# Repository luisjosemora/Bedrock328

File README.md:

# Bedrock328
Bedrock328 is an educational electronic board based on the ATmega328P microcontroller, designed to guide students and enthusiasts through every stage of embedded systems development — from through-hole soldering to bare-metal C programming and even Assembly coding.

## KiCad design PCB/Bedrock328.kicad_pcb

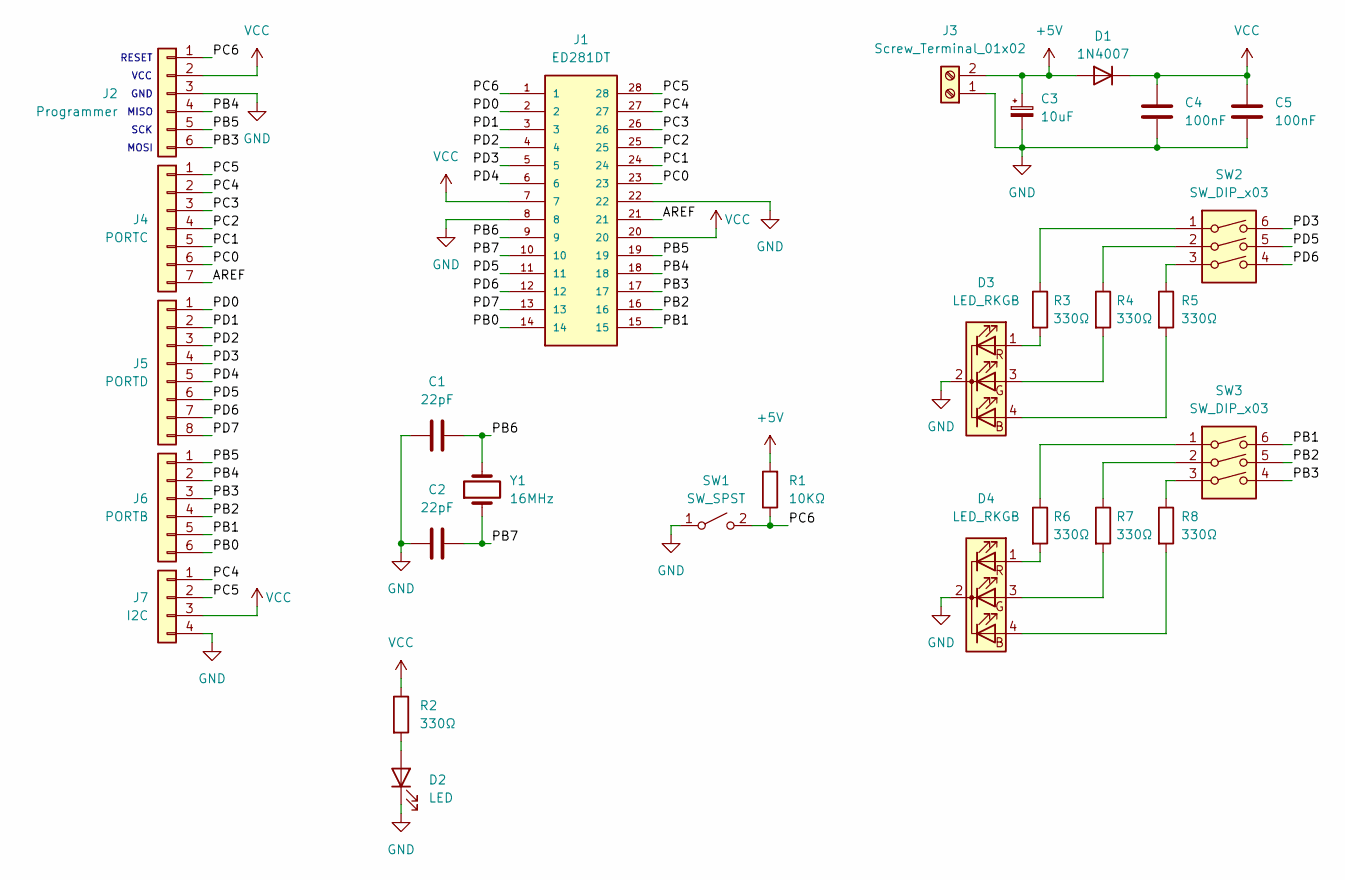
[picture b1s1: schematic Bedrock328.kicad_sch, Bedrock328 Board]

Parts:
C1, C2: 22pF; C_Disc_D5.0mm_W2.5mm_P5.00mm
C3: 10uF; CP_Radial_D8.0mm_P2.50mm
C4, C5: 100nF; C_Disc_D5.0mm_W2.5mm_P5.00mm
D1: 1N4007; D_DO-41_SOD81_P10.16mm_Horizontal
D2: LED; LED_D5.0mm
D3, D4: LED_RKGB; LED_D5.0mm-4_RGB
J1: ED281DT
J2: Programmer; PinHeader_1x06_P2.54mm_Vertical
J3: Screw_Terminal_01x02; KF301-2P
J4: PORTC; PinSocket_1x07_P2.54mm_Vertical
J5: PORTD; PinSocket_1x08_P2.54mm_Vertical
J6: PORTB; PinSocket_1x06_P2.54mm_Vertical
J7: I2C; PinSocket_1x04_P2.54mm_Vertical
R1: 10KΩ; R_Axial_DIN0207_L6.3mm_D2.5mm_P10.16mm_Horizontal
R2, R3, R4, R5, R6, R7, R8: 330Ω; R_Axial_DIN0207_L6.3mm_D2.5mm_P10.16mm_Horizontal
SW1: SW_SPST; SW_Tactile_6mm_round
SW2, SW3: SW_DIP_x03; SW_DIP_SPSTx03_Slide_9.78x9.8mm_W7.62mm_P2.54mm
Y1: 16MHz; Crystal_HC49-4H_Vertical

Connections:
+5V: C3.1, D1.2 (A), J3.2, R1.2
/AREF: J1.21, J4.7
/PB0: J1.14, J6.6
/PB1: J1.15, J6.5, SW3.6
/PB2: J1.16, J6.4, SW3.5
/PB3: J1.17, J2.6, J6.3, SW3.4
/PB4: J1.18, J2.4, J6.2
/PB5: J1.19, J2.5, J6.1
/PB6: C1.1, J1.9, Y1.2
/PB7: C2.1, J1.10, Y1.1
/PC0: J1.23, J4.6
/PC1: J1.24, J4.5
/PC2: J1.25, J4.4
/PC3: J1.26, J4.3
/PC4: J1.27, J4.2, J7.1
/PC5: J1.28, J4.1, J7.2
/PC6: J1.1, J2.1, R1.1, SW1.2 (B)
/PD0: J1.2, J5.1
/PD1: J1.3, J5.2
/PD2: J1.4, J5.3
/PD3: J1.5, J5.4, SW2.6
/PD4: J1.6, J5.5
/PD5: J1.11, J5.6, SW2.5
/PD6: J1.12, J5.7, SW2.4
/PD7: J1.13, J5.8
GND: C1.2, C2.2, C3.2, C4.2, C5.2, D2.1 (K), D3.2 (K), D4.2 (K), J1.8, J1.22, J2.3, J3.1, J7.4, SW1.1 (A)
unnamed: D2.2 (A), R2.2
unnamed: D3.4 (BA), R5.2
unnamed: D3.3 (GA), R4.2
unnamed: D3.1 (RA), R3.2
unnamed: D4.4 (BA), R8.2
unnamed: D4.3 (GA), R7.2
unnamed: D4.1 (RA), R6.2
unnamed: R3.1, SW2.1
unnamed: R4.1, SW2.2
unnamed: R5.1, SW2.3
unnamed: R6.1, SW3.1
unnamed: R7.1, SW3.2
unnamed: R8.1, SW3.3
VCC: C4.1, C5.1, D1.1 (K), J1.7, J1.20, J2.2, J7.3, R2.1

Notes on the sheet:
MOSI
VCC
SCK
RESET
GND
MISO

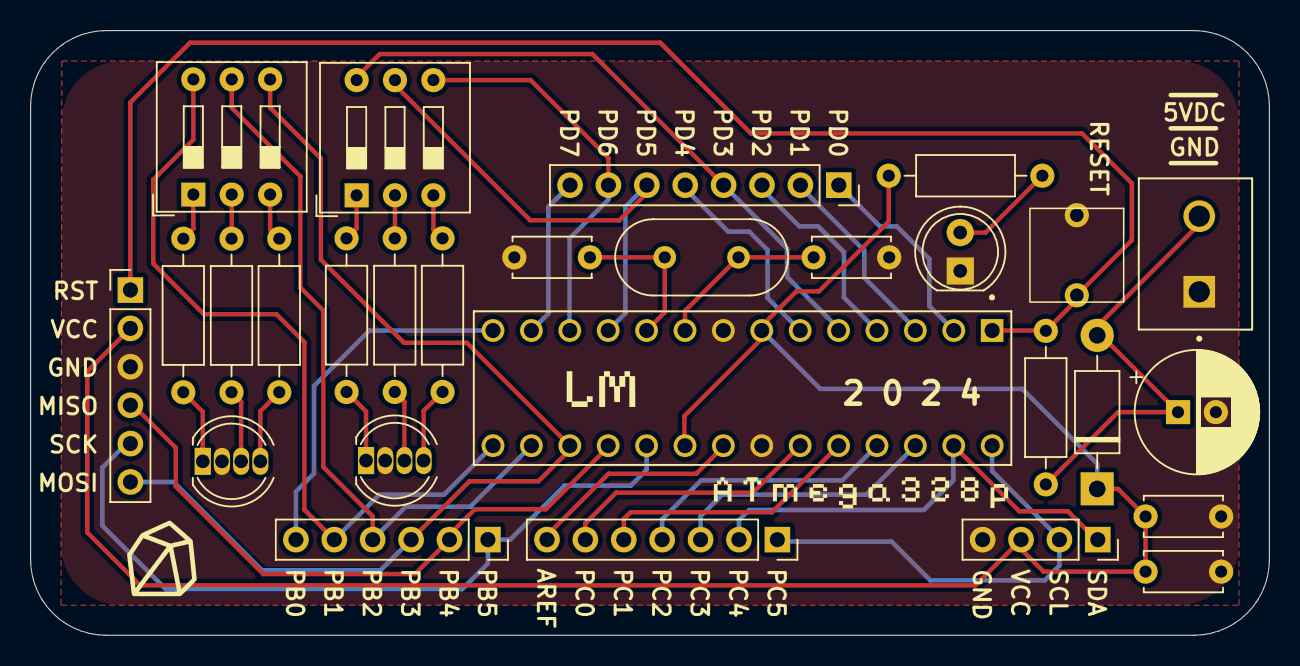
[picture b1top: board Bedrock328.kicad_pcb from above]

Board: 2 copper layers, 81.9 x 40.0 mm, 28 parts (0 on the bottom side), 40 nets.
